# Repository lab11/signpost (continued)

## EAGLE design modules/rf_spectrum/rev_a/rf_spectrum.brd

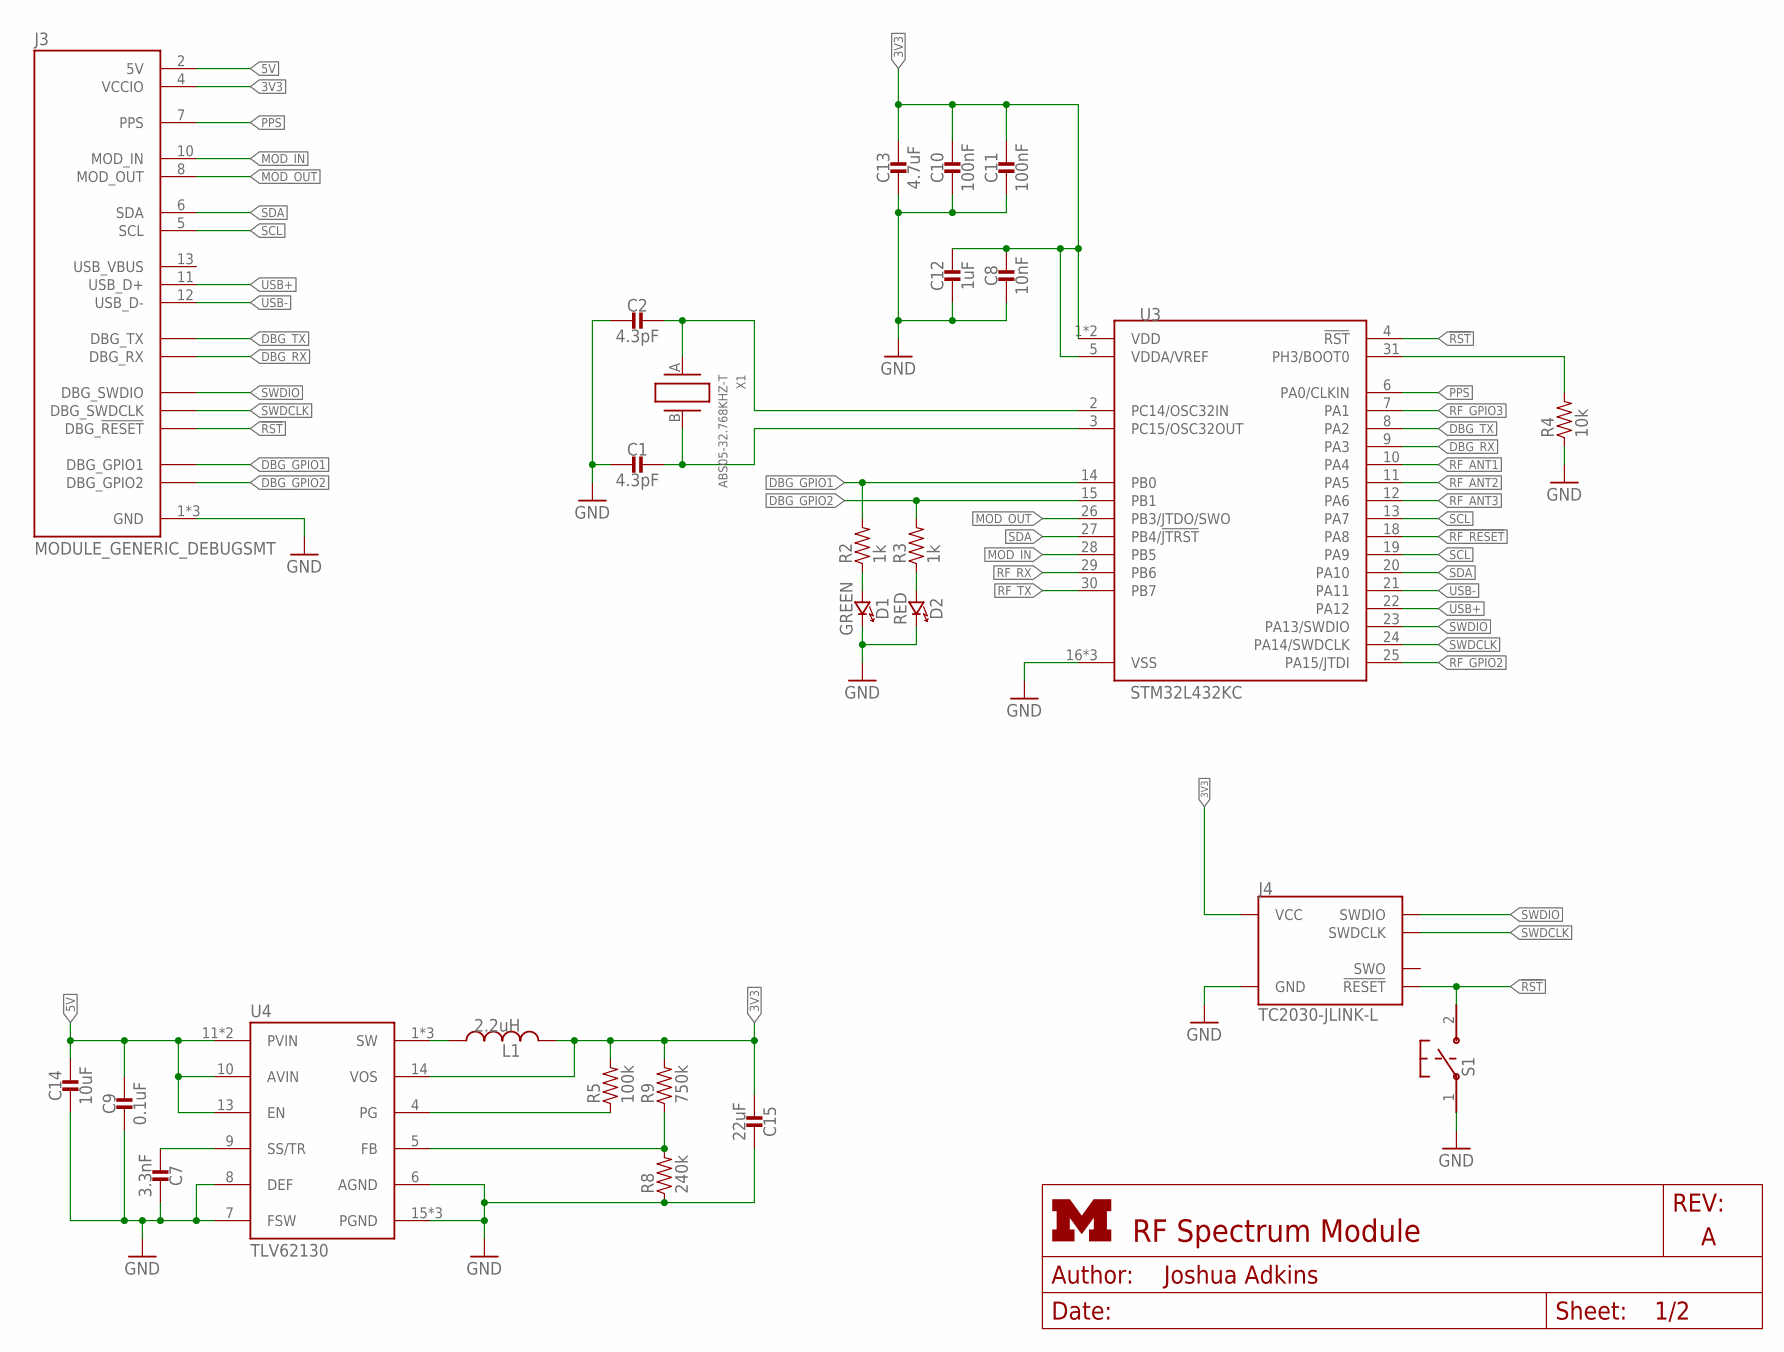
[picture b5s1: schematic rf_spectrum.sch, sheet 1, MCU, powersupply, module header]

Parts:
C1, C2: 4.3pF; 0402_CAP; DIGIKEY 490-6243-1-ND
C7: 3.3nF; 0603_CAP; DIGIKEY 490-1503-1-ND
C8: 10nF; 0402_CAP; DIGIKEY 490-4516-1-ND
C9: 0.1uF; 0603_CAP; DIGIKEY 490-1532-1-ND
C10, C11: 100nF; 0402_CAP; DIGIKEY 490-6328-1-ND
C12: 1uF; 0402_CAP; DIGIKEY 490-1320-1-ND
C13: 4.7uF; 0402_CAP; DIGIKEY 490-5915-1-ND
C14: 10uF; 0603_CAP; DIGIKEY 490-6405-1-ND
C15: 22uF; 0603_CAP; DIGIKEY 490-7611-1-ND
D1: GREEN; LED-0603; DIGIKEY 160-1446-1-ND
D2: RED; LED-0603; DIGIKEY 160-1447-1-ND
J3: MODULE_GENERIC_DEBUGSMT; MODULE_GENERIC_DEBUG_SMT
J4: TC2030-JLINK-L; TC2030-IDC
L1: 2.2uH; IHL-1212BZ-11
R2, R3: 1k; 0402_RES; DIGIKEY 311-1.0KJRCT-ND
R4: 10k; 0402_RES; DIGIKEY 311-1.0KJRCT-ND
R5: 100k; 0603-RES; DIGIKEY 311-100KGRCT-ND
R8: 240k; 0603-RES; DIGIKEY 311-240KGRCT-ND
R9: 750k; 0603-RES; DIGIKEY 311-750KGRCT-ND
S1: B3U-1000P
U3: STM32L432KC; UQFN-32
U4: TLV62130; TQFN-16/3MM
X1: ABS05-32.768KHZ-T; ABS05

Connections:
3V3: C8.1, C10.1, C11.1, C12.1, C13.1, C15.2, J3.4 (VCCIO), J4.1 (VCC), L1.P$2 (2), R5.2, R9.2, U3.1 (VDD), U3.5 (VDDA/VREF), U3.17 (VDD), U4.14 (VOS); also elsewhere on the board
3VSWOUT: L1.P$1 (1), U4.1 (SW), U4.2 (SW), U4.3 (SW)
5V: C9.1, C14.1, J3.2 (5V), U4.10 (AVIN), U4.11 (PVIN), U4.12 (PVIN), U4.13 (EN)
!RF_RESET: U3.18 (PA8); also elsewhere on the board
!RST: J3.20 (DBG_!RESET), J4.3 (!RESET), S1.2, U3.4 (!RST)
DBG_GPIO1: J3.16 (DBG_GPIO1), R2.2, U3.14 (PB0)
DBG_GPIO2: J3.19 (DBG_GPIO2), R3.2, U3.15 (PB1)
DBG_RX: J3.18 (DBG_RX), U3.9 (PA3)
DBG_TX: J3.17 (DBG_TX), U3.8 (PA2)
GND: C1.2, C2.2, C7.1, C8.2, C9.2, C10.2, C11.2, C12.2, C13.2, C14.2, C15.1, D1.C (CATHODE), D2.C (CATHODE), J3.1 (GND), J3.14 (GND), J3.15 (GND), J4.5 (GND), R4.1, R8.1, S1.1, U3.16 (VSS), U3.32 (VSS), U3.THERMAL (VSS), U4.6 (AGND), U4.7 (FSW), U4.8 (DEF), U4.15 (PGND), U4.16 (PGND), U4.GND; also elsewhere on the board
MOD_IN: J3.10 (MOD_IN), U3.28 (PB5)
MOD_OUT: J3.8 (MOD_OUT), U3.26 (PB3/JTDO/SWO)
unnamed: C2.1, U3.2 (PC14/OSC32IN), X1.A (1)
unnamed: C1.1, U3.3 (PC15/OSC32OUT), X1.B (2)
unnamed: R4.2, U3.31 (PH3/BOOT0)
unnamed: D1.A (ANODE), R2.1
unnamed: C7.2, U4.9 (SS/TR)
unnamed: R5.1, U4.4 (PG)
unnamed: R8.2, R9.1, U4.5 (FB)
PPS: J3.7 (PPS), U3.6 (PA0/CLKIN)
R3: D2.A (ANODE), R3.1
RF_ANT1: U3.10 (PA4); also elsewhere on the board
RF_ANT2: U3.11 (PA5); also elsewhere on the board
RF_ANT3: U3.12 (PA6); also elsewhere on the board
RF_GPIO2: U3.25 (PA15/JTDI); also elsewhere on the board
RF_GPIO3: U3.7 (PA1); also elsewhere on the board
RF_RX: U3.29 (PB6); also elsewhere on the board
RF_TX: U3.30 (PB7); also elsewhere on the board
SCL: J3.5 (SCL), U3.13 (PA7), U3.19 (PA9)
SDA: J3.6 (SDA), U3.20 (PA10), U3.27 (PB4/!JTRST)
SWDCLK: J3.21 (DBG_SWDCLK), J4.4 (SWDCLK), U3.24 (PA14/SWDCLK)
SWDIO: J3.22 (DBG_SWDIO), J4.2 (SWDIO), U3.23 (PA13/SWDIO)
USB+: J3.11 (USB_D+), U3.22 (PA12)
USB-: J3.12 (USB_D-), U3.21 (PA11)

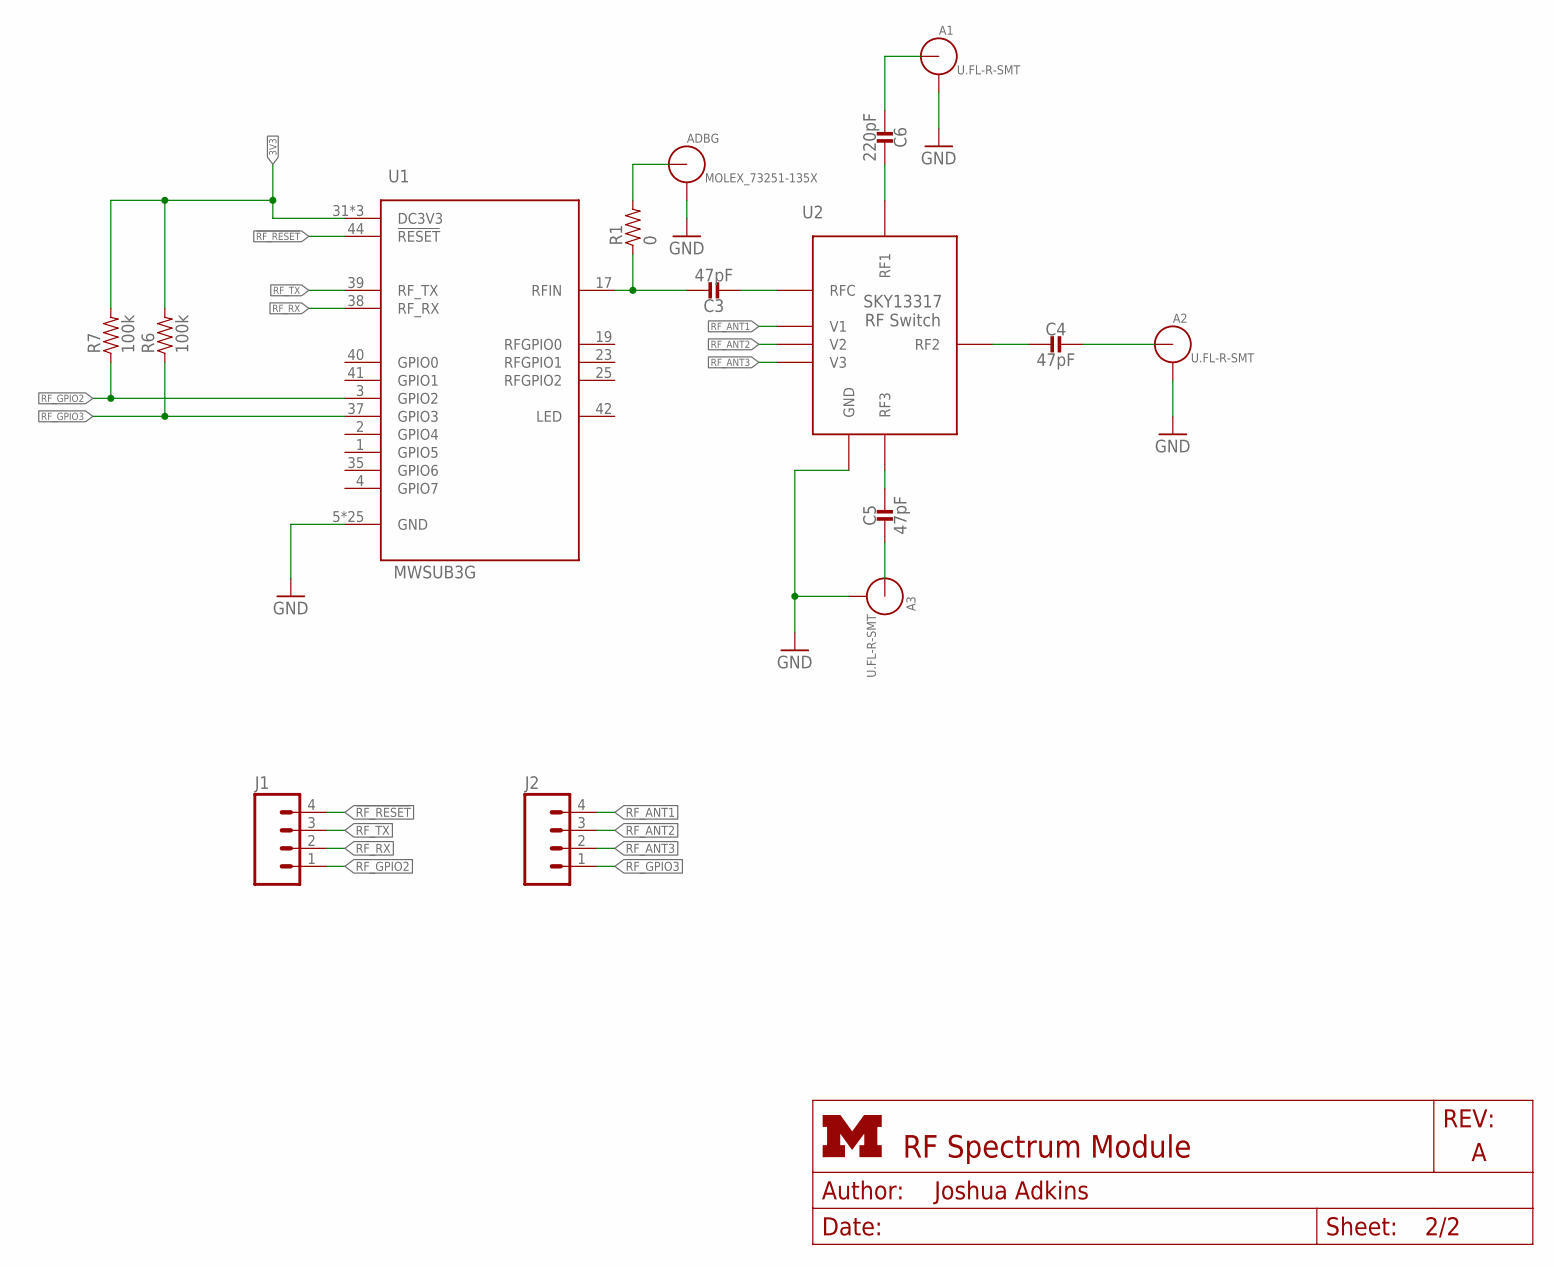
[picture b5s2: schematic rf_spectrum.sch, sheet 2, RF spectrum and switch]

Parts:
A1, A2, A3: U.FL-R-SMT; U.FL_SMT
ADBG: MOLEX_73251-135X; SMA-J/PCB
C3, C4, C5: 47pF; 0402_CAP; DIGIKEY 490-6241-1-ND
C6: 220pF; 0402_CAP; DIGIKEY 490-1293-1-ND
J1, J2: M04PTH; 1X04; DIGIKEY WM8086-ND
R1: 0; 0402_RES; DIGIKEY 311-0.0JRCT-ND
R6, R7: 100k; 0402_RES; DIGIKEY 311-100KLRCT-ND
U1: MWSUB3G
U2: SKY13317; XDFN-8

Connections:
3V3: R6.2, R7.2, U1.31 (DC3V3), U1.32 (DC3V3), U1.33 (DC3V3); also elsewhere on the board
!RF_RESET: J1.4, U1.44 (!RESET); also elsewhere on the board
GND: A1.GND1, A1.GND2, A2.GND1, A2.GND2, A3.GND1, A3.GND2, ADBG.2, ADBG.3, ADBG.4, ADBG.5, U1.5 (GND), U1.6 (GND), U1.7 (GND), U1.8 (GND), U1.9 (GND), U1.10 (GND), U1.11 (GND), U1.12 (GND), U1.13 (GND), U1.14 (GND), U1.15 (GND), U1.16 (GND), U1.18 (GND), U1.20 (GND), U1.21 (GND), U1.22 (GND), U1.24 (GND), U1.26 (GND), U1.27 (GND), U1.28 (GND), U1.29 (GND), U1.34 (GND), U1.43 (GND), U1.45 (GND), U1.46 (GND), U2.P$1 (GND); also elsewhere on the board
unnamed: C3.1, R1.1, U1.17 (RFIN)
unnamed: C3.2, U2.1 (RFC)
unnamed: C6.1, U2.4 (RF1)
unnamed: A1.SIG (ANT), C6.2
unnamed: C4.2, U2.5 (RF2)
unnamed: A2.SIG (ANT), C4.1
unnamed: C5.1, U2.8 (RF3)
unnamed: A3.SIG (ANT), C5.2
unnamed: ADBG.1 (ANT), R1.2
RF_ANT1: J2.4, U2.3 (V1); also elsewhere on the board
RF_ANT2: J2.3, U2.6 (V2); also elsewhere on the board
RF_ANT3: J2.2, U2.7 (V3); also elsewhere on the board
RF_GPIO2: J1.1, R7.1, U1.3 (GPIO2); also elsewhere on the board
RF_GPIO3: J2.1, R6.1, U1.37 (GPIO3); also elsewhere on the board
RF_RX: J1.2, U1.38 (RF_RX); also elsewhere on the board
RF_TX: J1.3, U1.39 (RF_TX); also elsewhere on the board

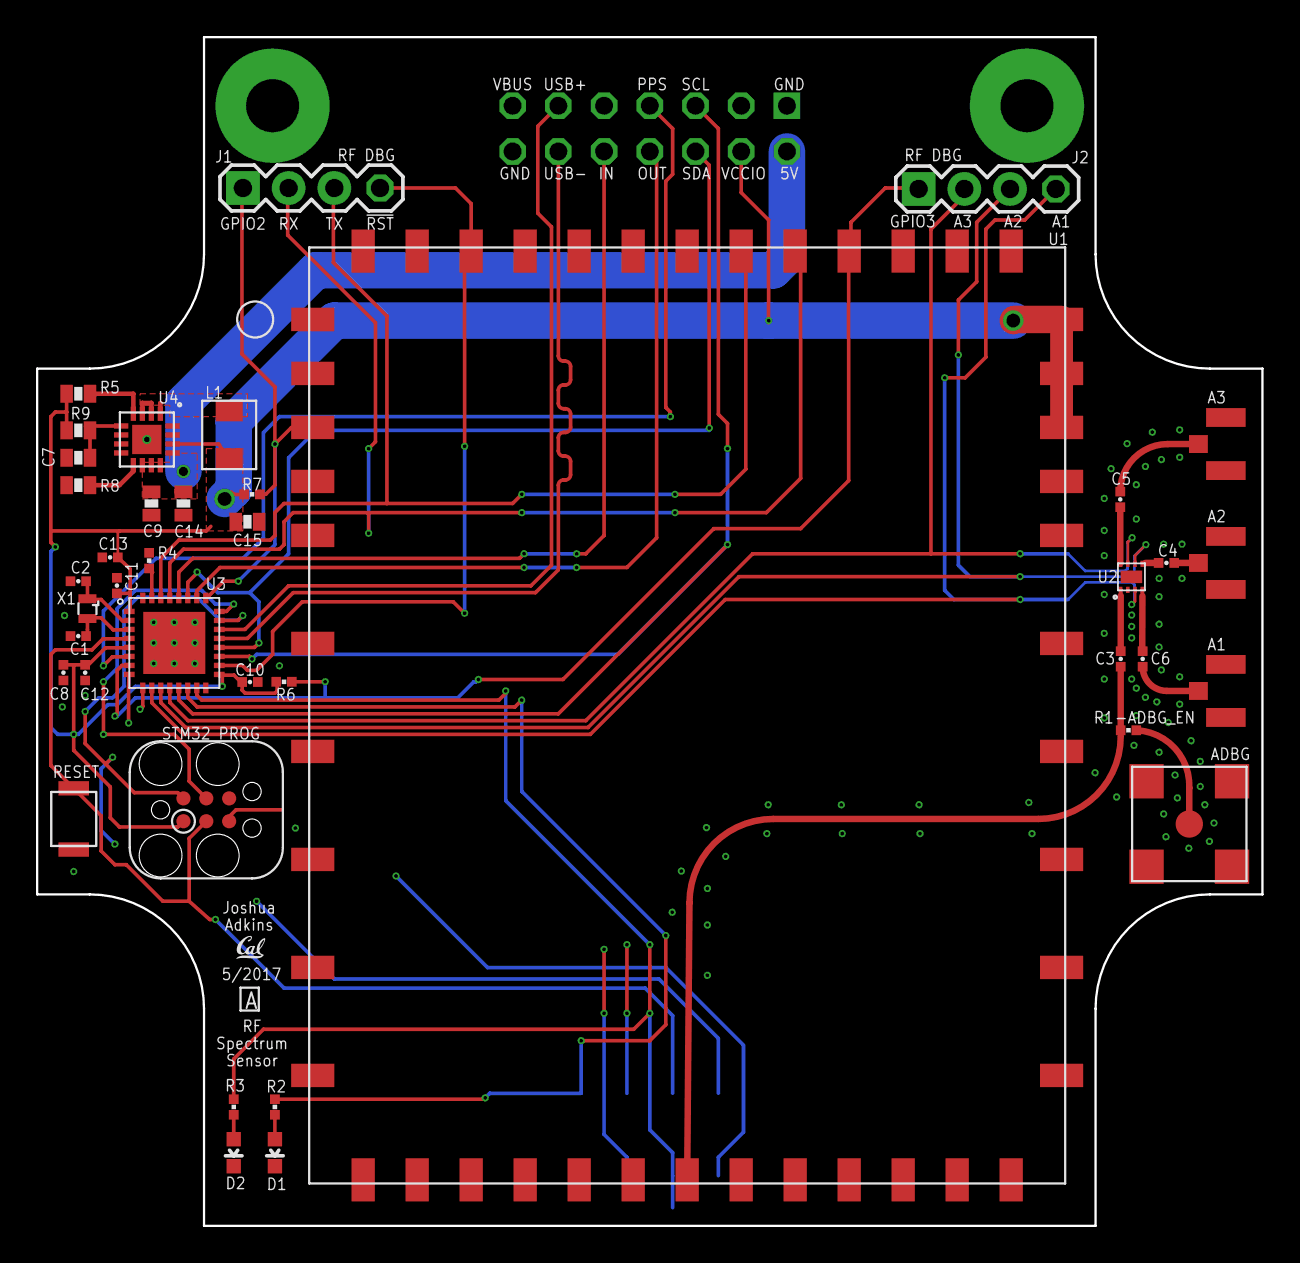
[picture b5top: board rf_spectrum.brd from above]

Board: 4 copper layers, 68.1 x 66.0 mm, 42 parts (0 on the bottom side), 43 nets.

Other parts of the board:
U$2: UCB_CAL_50MIL

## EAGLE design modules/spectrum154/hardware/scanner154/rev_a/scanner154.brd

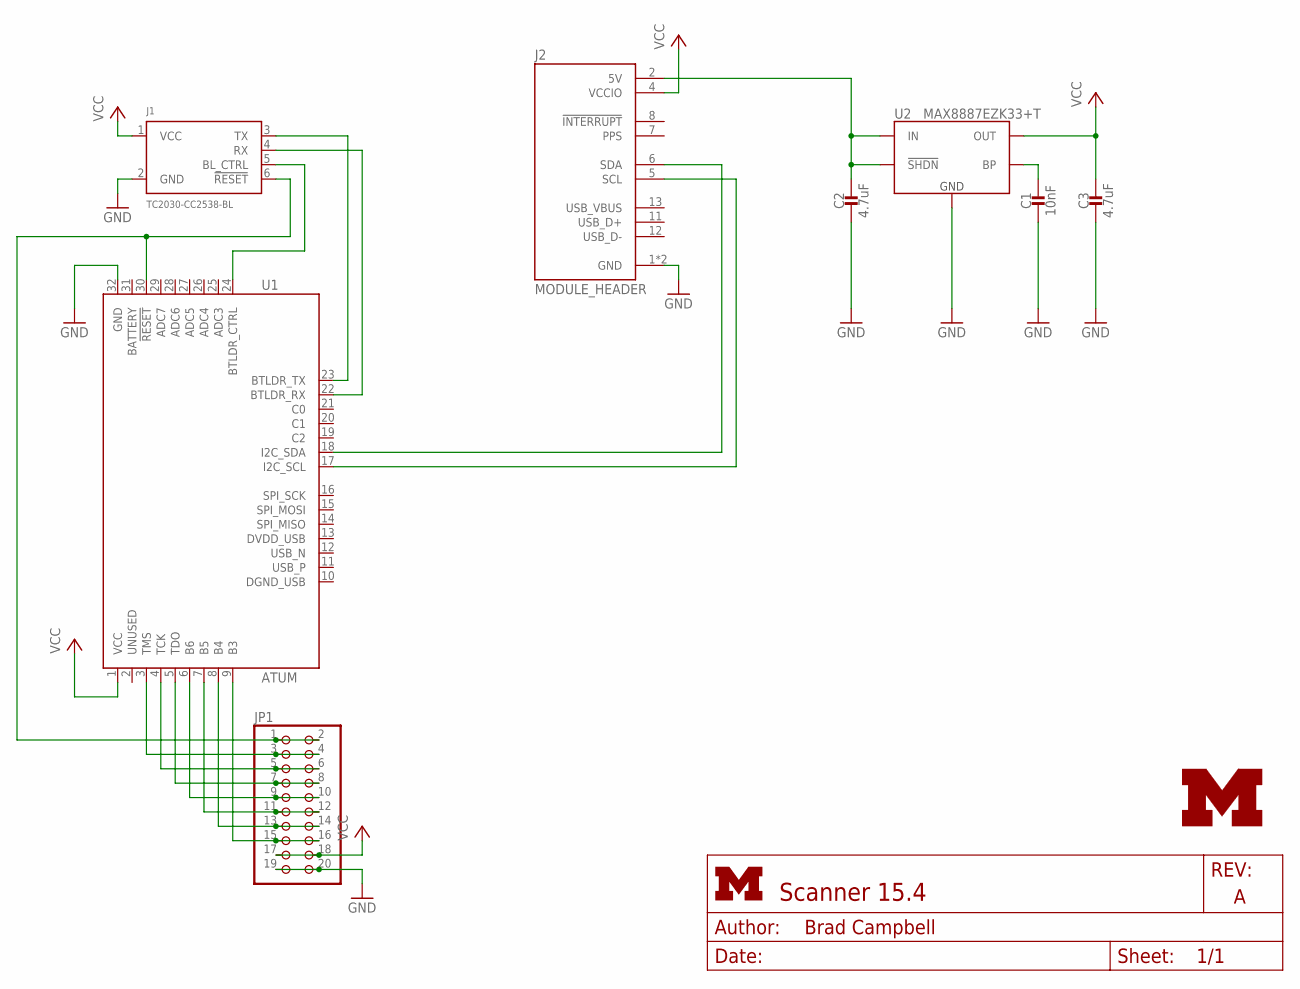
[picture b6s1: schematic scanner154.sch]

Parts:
C1: 10nF; 0603_CAP; DIGIKEY 490-1512-1-ND
C2, C3: 4.7uF; 0603_CAP; DIGIKEY 490-3297-1-ND
J1: TC2030-CC2538-BL; TC2030-IDC
J2: MODULE_HEADER; HEADER_14PIN
JP1: PINHD-2X10; 2X10
LOGO2: UMICH_SOLID_HUGE; UMICH_SOLID_500MIL
U1: ATUM
U2: MAX8887EZK33+T; SOT-23-5

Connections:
5V: C2.1, J2.2 (5V), U2.1 (IN), U2.3 (!SHDN)
!RESET: J1.6 (!RESET), JP1.1, JP1.2, U1.30 (!RESET)
B3: JP1.15, JP1.16, U1.9 (B3)
B4: JP1.13, JP1.14, U1.8 (B4)
B5: JP1.11, JP1.12, U1.7 (B5)
B6: JP1.9, JP1.10, U1.6 (B6)
GND: C1.2, C2.2, C3.2, J1.2 (GND), J2.1 (GND), J2.14 (GND), JP1.19, JP1.20, U1.32 (GND), U2.2 (GND)
unnamed: J1.3 (TX), U1.23 (BTLDR_TX)
unnamed: J1.4 (RX), U1.22 (BTLDR_RX)
unnamed: J1.5 (BL_CTRL), U1.24 (BTLDR_CTRL)
unnamed: C1.1, U2.4 (BP)
SCL: J2.5 (SCL), U1.17 (I2C_SCL)
SDA: J2.6 (SDA), U1.18 (I2C_SDA)
TCK: JP1.5, JP1.6, U1.4 (TCK)
TDO: JP1.7, JP1.8, U1.5 (TDO)
TMS: JP1.3, JP1.4, U1.3 (TMS)
VCC: C3.1, J1.1 (VCC), J2.4 (VCCIO), JP1.17, JP1.18, U1.1 (VCC), U2.5 (OUT)

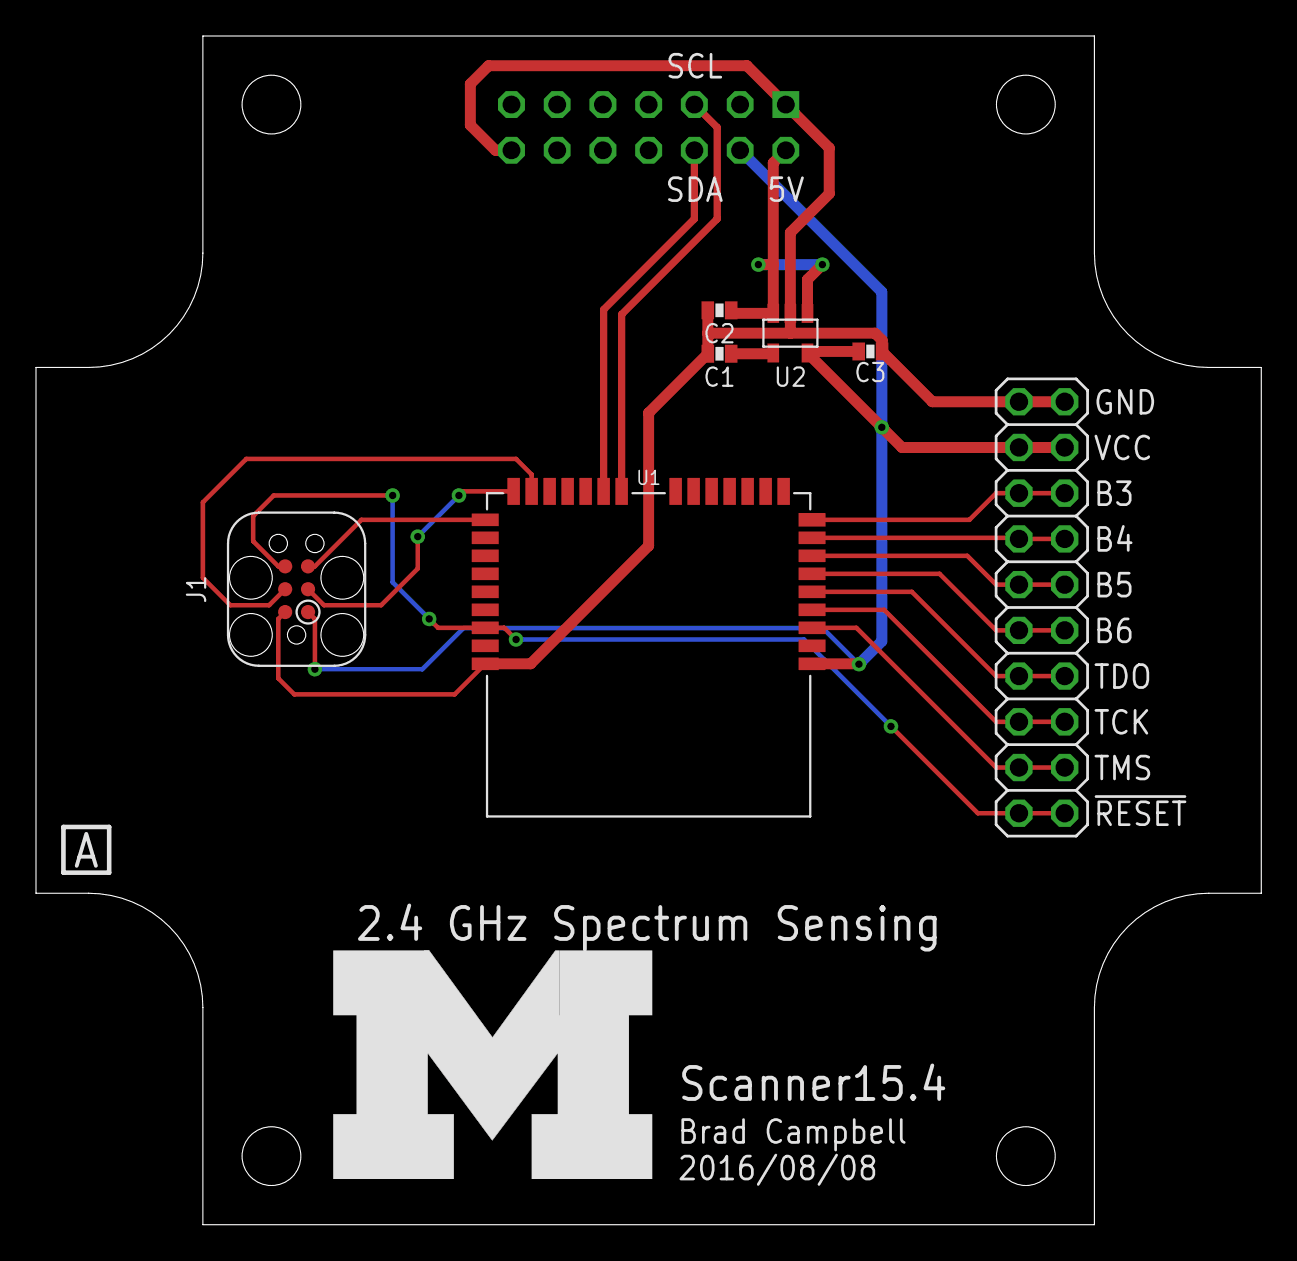
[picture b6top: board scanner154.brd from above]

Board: 2 copper layers, 68.1 x 66.0 mm, 9 parts (0 on the bottom side), 17 nets.
